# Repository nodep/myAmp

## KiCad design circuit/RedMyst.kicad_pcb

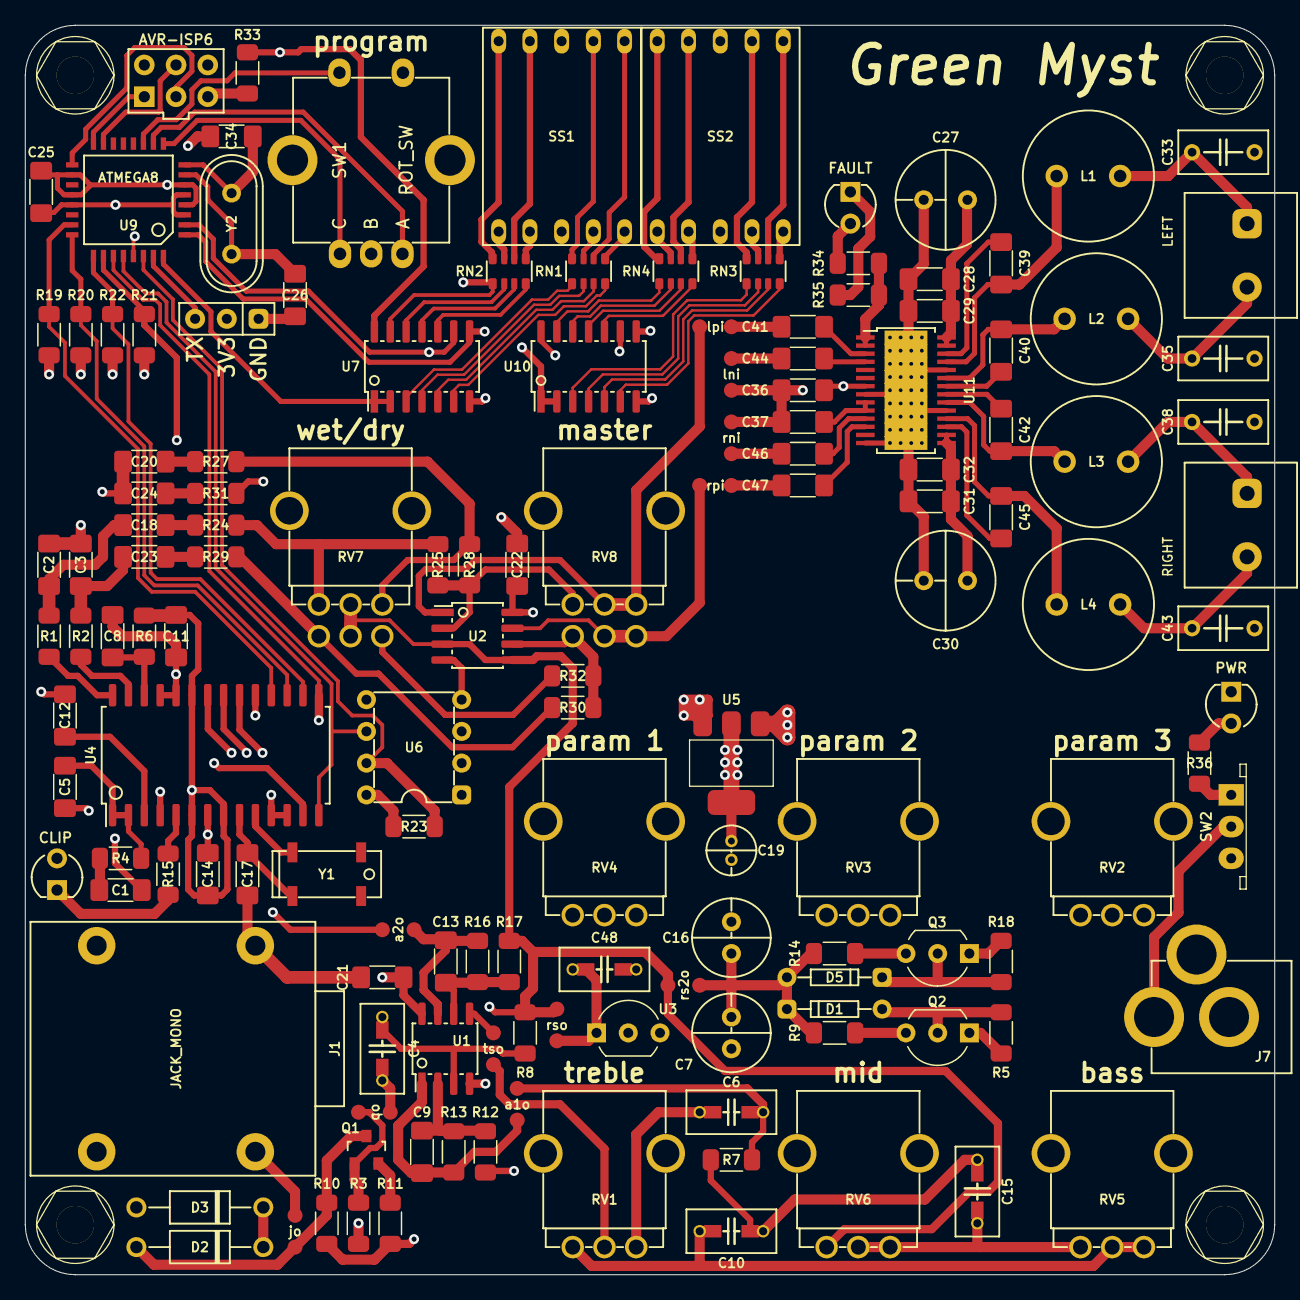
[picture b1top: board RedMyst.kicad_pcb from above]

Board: 4 copper layers, 100.0 x 100.0 mm, 146 parts (0 on the bottom side), 133 nets.

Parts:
C1, C8, C12, C18, C20, C23, C24: 1µF; C_1206
C2, C3: 10nF; C_1206
C4: 1μF; C_5MM_1206
C5, C9, C13, C29, C32: 1nF; C_1206
C6: 250pF; C_5MM_1206
C7, C16: 220μF; CPOL_D6.3_P2.5
C10, C48: 100nF; C_5MM_1206
C11, C14, C21, C22, C25, C28, C31: 100nF; C_1206
C15: 47nF; C_5MM_1206
C17: 15pF; C_1206
C19: 10µf; CPOL_D4_P1.5
C26, C34: 22pF; C_1206
C27, C30: 100μF; CPOL_D8_P3.5
C33, C35, C38, C43: 680nF; C_FILM_5MM
C36, C37, C41, C44, C46, C47: 1μF; C_1206
C39, C40, C42, C45: 220nF; C_1206
D1, D5: 1N4148; DO35
D2, D3: 1N4773a; DO41
D4: CLIP; LED_D3.0mm
D7: FAULT; LED_D3.0mm
D8: PWR; LED_D3.0mm
J1: JACK_MONO; JACK_CL13106
J2: CONN_01X03; PIN_1x03
J3, J4, J5, J6: HOLE; MountingHole
J7: Barrel_Jack_Switch; POWER_JACK_2.1mm
L1, L2, L3, L4: 10μH; COILCRAFT_DR0810
NB1: qo; NET_BRK
NB2: a1o; NET_BRK
NB3: jo; NET_BRK
NB4: tso; NET_BRK
NB5: a2o; NET_BRK
NB6: rso; NET_BRK
NB10: rs2o; NET_BRK
NB16: lpi; NET_BRK
NB17: lni; NET_BRK
NB18: rni; NET_BRK
NB19: rpi; NET_BRK
Q1: MMBFJ201; SOT-23
Q2: BC547; TO-92_Inline_Wide
Q3: BC557; TO-92_Inline_Wide
R1, R2, R4, R12, R17: 1K; R_1206
R3, R11: 1; R_1206
R5, R18: 4K7; R_1206
R6, R15: 100; R_1206
R7: 100K; R_1206
R8, R10: 1M; R_1206
R9, R14: 10; R_1206
R13, R16, R19, R20, R21, R22, R23, R24, R25, R27, R28, R29, R30, R31, R32, R33, R34: 10K; R_1206
R35, R36: 2K2; R_1206
RN1, RN2, RN3, RN4: 100; R_Array_x4_1206
RV1, RV5: 250K; ALPS_RK09L
RV2, RV3, RV4: 50K; ALPS_RK09L
RV6: 10K; ALPS_RK09L
RV7, RV8: 10K; ALPS_RK09L_DBL
S1: LEFT; SPKR_5MM
S2: RIGHT; SPKR_5MM
SS1, SS2: SEVSEG; 7seg_14.2mm
SW1: ROT_SW; ROT_ENC
SW2: ON/OFF; ESP2010_switch
U1, U2: NE5532; SOIC-8_3.9x4.9mm_P1.27mm
U3: TLE2426; TO-92_Inline_Wide
U4: FV-1; SOIC-28_7.5x17.9mm_Pitch1.27mm
U5: LM1117; SOT-223
U6: 24LC32A; DIP-8
U7, U10: 74164; SOIC-14_3.9x8.7mm_P1.27mm
U8: AVR-ISP6; AVR_ISP6
U9: ATMEGA8; TQFP-32_7x7mm_Pitch0.8mm
U11: TPA3136D2; HTSSOP-28_4.4x9.7mm_Pitch0.65mm_ThermalPad
Y1: 32768Hz; QUARTZ_85SMX
Y2: 8MHz; Crystal_HC49-U_Vertical

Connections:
+3V3: C11.1, C14.2, C19.1, C25.2, D4.2, J2.2, R6.1, R21.2, R23.2, R33.2, RV2.1, RV3.1, RV4.1, U4.6, U4.8, U4.23, U5.2, U6.8, U7.14, U8.2, U9.4, U9.6, U9.18, U9.20, U10.14
/AVR_RST: R33.1, U8.5, U9.29
/DBG_TX: J2.3, U9.31
/FV_LOUT: C2.1, C18.1, R1.1
/FV_ROUT: C3.1, C23.1, R2.1
/GVDD: C37.1, U11.9, U11.10
/LED_CK: U7.8, U9.1, U10.8
/LED_DT: U7.1, U7.2, U9.32
/LED_RST: U7.9, U9.2, U10.9
/MID: C12.2, U4.3
/MISO: U8.1, U9.16
/MOSI: U8.4, U9.15
/ROT_SW: SW1.4, U9.11
/S0: R22.1, U4.16, U9.25
/S1: R20.2, U4.17, U9.24
/S2: R19.1, U4.18, U9.23
/SCK: U8.3, U9.17
/SCL: U4.14, U6.6, U9.28
/SDA: U4.15, U6.5, U9.27
/SD_FAULT: R34.2, R35.1, U11.1, U11.2
/T0: R21.1, U4.13, U9.26
/TONE_OUT: C1.2, C20.1, C24.1, NB5.1
/WP: R23.1, U6.7, U9.30
GND: C2.2, C3.2, C5.1, C8.2, C11.2, C12.1, C14.1, C16.2, C17.2, C19.2, C21.1, C22.1, C25.1, C26.2, C27.2, C28.2, C29.2, C30.2, C31.2, C32.2, C33.1, C34.2, C35.2, C36.2, C37.2, C38.1, C43.2, C48.1, D3.2, D8.1, J1.1, J1.3, J1.4, J2.1, J7.2, J7.3, NB17.2, NB18.2, Q3.1, R10.2, R11.2, R18.1, R19.2, R20.1, R22.2, RV2.3, RV3.3, RV4.3, SS1.3, SS1.8, SS2.3, SS2.8, SW1.2, SW1.5, U1.4, U2.4, U3.2, U4.4, U4.7, U4.11, U4.12, U4.19, U4.24, U4.25, U5.1, U6.1, U6.2, U6.3, U6.4, U7.7, U8.6, U9.3, U9.5, U9.21, U10.7, U11.8, U11.14, U11.19, U11.24, U11.29
LOUT: NB16.2, RV8.2, RV8.3, U2.1
unnamed: C1.1, R4.1
unnamed: C4.1, R8.1, U1.3
unnamed: C4.2, NB1.1
unnamed: C5.2, R4.2, U4.1, U4.2
unnamed: C6.1, RV1.3
unnamed: C6.2, NB2.1, R7.2
unnamed: C8.1, R6.2, U4.26
unnamed: C9.1, NB2.2, R13.2, U1.1
unnamed: C9.2, R12.2, R13.1, U1.2
unnamed: C10.1, RV1.1, RV5.2, RV5.3
unnamed: C10.2, C15.1, R7.1
unnamed: C13.1, NB5.2, R16.2, U1.7
unnamed: C13.2, R16.1, R17.1, U1.6
unnamed: C15.2, RV5.1, RV6.2, RV6.3
unnamed: C7.2, C16.1, D1.1, D5.2, NB10.2, R9.1, R14.2
unnamed: C17.1, U4.9, Y1.1
unnamed: C18.2, R24.1
unnamed: C20.2, R27.1
unnamed: C23.2, R29.1
unnamed: C24.2, R31.1
unnamed: C26.1, U9.7, Y2.1
unnamed: C33.2, L1.2, S1.1
unnamed: C34.1, U9.8, Y2.2
unnamed: C35.1, L2.2, S1.2
unnamed: C38.2, L3.2, S2.1
unnamed: C39.1, L1.1, U11.25
unnamed: C39.2, U11.26
unnamed: C40.1, L2.1, U11.23
unnamed: C40.2, U11.22
unnamed: C41.1, U11.3
unnamed: C41.2, NB16.1
unnamed: C42.1, L3.1, U11.20
unnamed: C42.2, U11.21
unnamed: C43.1, L4.2, S2.2
unnamed: C44.1, U11.4
unnamed: C44.2, NB17.1
unnamed: C45.1, L4.1, U11.18
unnamed: C45.2, U11.17
unnamed: C46.1, U11.11
unnamed: C46.2, NB18.1
unnamed: C47.1, U11.12
unnamed: C47.2, NB19.1
unnamed: C48.2, NB6.2, U3.1
unnamed: D1.2, Q2.2, R5.1
unnamed: D2.1, D3.1
unnamed: D2.2, NB3.1, Q1.3, R10.1
unnamed: D4.1, R15.1
unnamed: D5.1, Q3.2, R18.2
unnamed: D7.1, R35.2
unnamed: D8.2, R36.2
unnamed: J1.6, NB3.2
unnamed: J7.1, SW2.2
unnamed: NB1.2, Q1.1, R3.1
unnamed: NB4.1, U1.5
unnamed: NB4.2, RV1.2
unnamed: Q1.2, R11.1
unnamed: Q2.3, R9.2
unnamed: Q3.3, R14.1
unnamed: R1.2, U4.28
unnamed: R2.2, U4.27
unnamed: R15.2, U4.5
unnamed: R24.2, R25.1, RV7.1
unnamed: R25.2, R28.2, RV8.1, U2.2
unnamed: R27.2, R28.1, RV7.3
unnamed: R29.2, R30.1, RV7.4
unnamed: R30.2, R32.2, RV8.4, U2.6
unnamed: R31.2, R32.1, RV7.6
unnamed: RN1.1, U7.3
unnamed: RN1.2, U7.4
unnamed: RN1.3, U7.5
unnamed: RN1.4, U7.6
unnamed: RN1.5, SS1.5
unnamed: RN1.6, SS1.6
unnamed: RN1.7, SS1.4
unnamed: RN1.8, SS1.7
unnamed: RN2.1, U7.13, U10.1, U10.2
unnamed: RN2.2, U7.12
unnamed: RN2.3, U7.11
unnamed: RN2.4, U7.10
unnamed: RN2.5, SS1.2
unnamed: RN2.6, SS1.9
unnamed: RN2.7, SS1.1
unnamed: RN2.8, SS1.10
unnamed: RN3.1, U10.3
unnamed: RN3.2, U10.4
unnamed: RN3.3, U10.5
unnamed: RN3.4, U10.6
unnamed: RN3.5, SS2.5
unnamed: RN3.6, SS2.6
unnamed: RN3.7, SS2.4
unnamed: RN3.8, SS2.7
unnamed: RN4.1, U10.13
unnamed: RN4.2, U10.12
unnamed: RN4.3, U10.11
unnamed: RN4.4, U10.10
unnamed: RN4.5, SS2.2
unnamed: RN4.6, SS2.9
unnamed: RN4.7, SS2.1
unnamed: RN4.8, SS2.10
unnamed: RV2.2, U4.22
unnamed: RV3.2, U4.21
unnamed: RV4.2, U4.20
unnamed: SW1.1, U9.10
unnamed: SW1.3, U9.9
unnamed: U4.10, Y1.2
ROUT: NB19.2, RV8.5, RV8.6, U2.7
VDD: C7.1, C21.2, C22.2, C27.1, C28.1, C29.1, C30.1, C31.1, C32.1, C36.1, D7.2, Q2.1, R3.2, R5.2, R34.1, R36.1, SW2.1, U1.8, U2.8, U3.3, U5.3, U11.7, U11.15, U11.16, U11.27, U11.28
VGND: NB6.1, NB10.1, R8.2, R12.1, R17.2, RV6.1, RV7.2, RV7.5, U2.3, U2.5

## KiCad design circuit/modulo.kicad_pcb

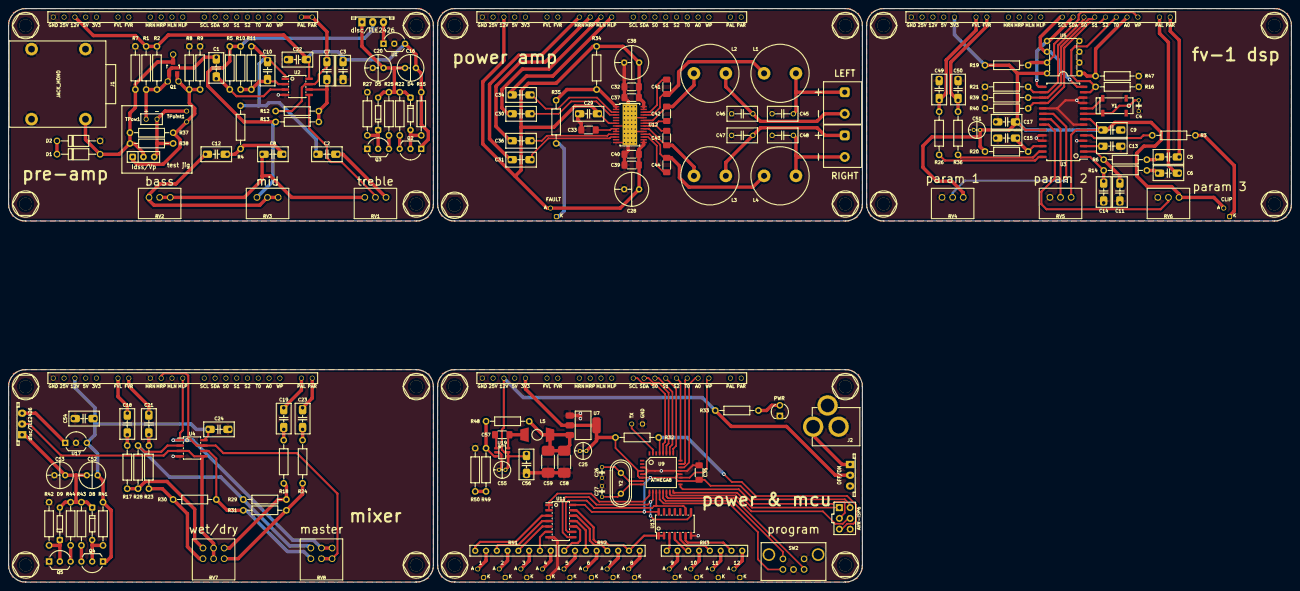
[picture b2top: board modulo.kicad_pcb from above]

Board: 2 copper layers, 302.0 x 135.0 mm, 201 parts (0 on the bottom side), 150 nets.

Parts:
C1, C29, C30, C31, C34, C36: 1μF; C_5MM_1206
C2: 680pF; C_5MM_1206
C3, C9, C17, C22, C24, C54, C56: 100nF; C_5MM_1206
C4: 15pF; C_2.5MM
C5, C6, C13, C15, C18, C19, C21, C23: 1µF; C_5MM_1206
C7, C10, C11, C14: 1nF; C_5MM_1206
C8: 250nF; C_5MM_1206
C12: 47nF; C_5MM_1206
C16, C20, C52, C53: 220μF; CPOL_D6.3_P2.5
C25: 10µf; CPOL_D4_P1.5
C26, C27: 22pF; C_2.5MM
C28, C38: 100μF; CPOL_D8_P3.5
C32, C35, C39, C57: 100nF; C_1206
C33: 1μF; C_1206
C37, C40: 1nF; C_1206
C41, C42, C43, C44: 220nF; C_1206
C45, C46, C47, C48: 680nF; C_FILM_5MM
C49, C50: 10nF; C_5MM_1206
C51: 10µF; CPOL_D4_P1.5
C55: 4.7µf; CPOL_D4_P1.5
C58, C59: 15µf; C_1812
D1, D2: 1N4773a; DO41
D3: CLIP; LED_D3.0mm_PCBedge
D4, D5, D8, D9: 1N4148; DO35
D6: FAULT; LED_D3.0mm_PCBedge
D7: PWR; LED_D3.0mm
D10: 1; LED_D3.0mm_PCBedge
D11: 2; LED_D3.0mm_PCBedge
D12: 3; LED_D3.0mm_PCBedge
D13: 4; LED_D3.0mm_PCBedge
D14: 5; LED_D3.0mm_PCBedge
D15: 6; LED_D3.0mm_PCBedge
D16: 7; LED_D3.0mm_PCBedge
D17: 8; LED_D3.0mm_PCBedge
D18: 9; LED_D3.0mm_PCBedge
D19: 10; LED_D3.0mm_PCBedge
D20: 11; LED_D3.0mm_PCBedge
D21: 12; LED_D3.0mm_PCBedge
J1: JACK_MONO; JACK_CL13106
J2: Barrel_Jack_Switch; POWER_JACK_2.1mm
J3, J4, J5, J6, J7, J8, J9, J10, J11, J12, J13, J14, J15, J17, J18, J19, J24, J25, J26, J27: HOLE; MountingHole
L1, L2, L3, L4: 10μH; COILCRAFT_RFS1412
L5: 33µH; COIL_SRR6603
Q1: MMBFJ201; SOT-23_with_jig
Q2, Q4: BC547; TO-92_Inline_Wide
Q3, Q5: BC557; TO-92_Inline_Wide
R1: 15K; R_10MM
R2, R5, R7, R9, R37: 1M; R_10MM
R3, R20, R38: 100; R_10MM
R4: 100K; R_10MM
R6, R10, R13, R14, R26, R36: 1K; R_10MM
R8: 1K5; R_10MM
R11, R12, R16, R17, R18, R19, R21, R23, R24, R28, R29, R30, R31, R32, R34, R39, R40, R47, R49, R50: 10K; R_10MM
R15, R27, R41, R42: 4K7; R_10MM
R22, R25, R43, R44: 10; R_10MM
R33, R35: 2K2; R_10MM
R48: 75K; R_10MM
RN1, RN2, RN3: 100; R_Array_x4_P2.54
RV1, RV2: A100K; BOURNS_PTD901_xx15K
RV3: 10K; BOURNS_PTD901_xx15K
RV4, RV5, RV6: 50K; BOURNS_PTD901_xx15K
RV7, RV8: 10K; BOURNS_PTD902_xx15K
S1: LEFT; SPKR_5MM
S2: RIGHT; SPKR_5MM
SW1: OFF/ON; ESP2010_switch
SW2: ROT_SW; BOURNS_PEC12R_2x17F
SW3: Idss/Vp; PIN_1x03
SW4, SW5: disc/TLE2426; ESP2010_switch
TPoint1: CONN_01X02; TestPoints
TPow1: TestDC; TestPower
U1, U17: TLE2426; TO-92_Inline_Wide
U2, U4: NE5532; SOIC-8_3.9x4.9mm_P1.27mm
U3: FV-1; SOIC-28_7.5x17.9mm_Pitch1.27mm
U5: 24LC32A; DIP-8
U6, U8, U14, U15, U16: modulo-bus
U7: LM1117; SOT-223
U9: ATMEGA8; TQFP-32_7x7mm_Pitch0.8mm
U10: AVR-ISP6; AVR_ISP6_horizontal
U11, U13: 74164; SOIC-14_3.9x8.7mm_P1.27mm
U12: TPA3136D2; HTSSOP-28_4.4x9.7mm_Pitch0.65mm_ThermalPad
U18: DBG_UART
U19: TPS560430; SOT-23-6
Y1: 32768Hz; QUARTZ_85SMX
Y2: 8MHz; Crystal_HC49-U_Vertical

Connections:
+3V3: C9.2, C17.1, C25.1, C35.2, C51.1, D3.2, R19.2, R20.1, R32.2, RV4.3, RV5.3, RV6.3, U3.6, U3.8, U3.23, U5.8, U7.2, U8.5, U9.4, U9.6, U9.18, U9.20, U10.2, U11.14, U13.14, U15.5
+12V: C3.2, C16.1, C22.2, C24.2, C28.1, C29.1, C32.1, C37.1, C38.1, C39.1, C40.1, C52.1, C54.2, C55.1, C56.1, D6.2, Q2.1, Q4.1, R1.2, R2.2, R15.2, R33.1, R34.1, R41.2, SW1.2, U1.3, U2.8, U4.8, U6.3, U8.3, U12.7, U12.15, U12.16, U12.27, U12.28, U14.3, U16.3, U17.3, U19.4, U19.5
/Class D audio power amp/GVDD: C33.1, U12.9, U12.10
/Class D audio power amp/SD_FAULT: R34.2, R35.1, U12.1, U12.2
/FV-1/A0: R47.1, U5.1, U15.20
/FV-1/FV_LIN: C6.2, U15.6
/FV-1/FV_LOUT: C49.1, R26.1, U15.8
/FV-1/FV_RIN: C5.2, U15.7
/FV-1/FV_ROUT: C50.1, R36.1, U15.9
/FV-1/MID: C13.2, U3.3
/FV-1/REFP: C15.1, R20.2, U3.26
/FV-1/S0: R21.1, U3.16, U15.12
/FV-1/S1: R39.2, U3.17, U15.13
/FV-1/S2: R40.1, U3.18, U15.14
/FV-1/SCL: U3.14, U5.6, U15.10
/FV-1/SDA: U3.15, U5.5, U15.11
/FV-1/T0: R16.1, U3.13, U15.15
/FV-1/WP: R19.1, U5.7, U15.21
/mixer/FVL: C18.1, U16.8
/mixer/FVR: C21.1, U16.9
/mixer/MIXL: RV8.2, RV8.3, U4.1, U16.16
/mixer/MIXR: RV8.5, RV8.6, U4.7, U16.18
/mixer/MIX_VGND: RV7.2, RV7.5, SW5.2, U4.3, U4.5
/mixer/PAL: C19.1, U16.6
/mixer/PAR: C23.1, U16.7
/mixer/vgnd_disc: C52.2, C53.1, D8.1, D9.2, R43.1, R44.2, SW5.1
/mixer/vgnd_tle: SW5.3, U17.1
/power and MCU/4.75V: C58.1, C59.1, L5.2, R48.2, U7.3
/power and MCU/A0: U8.20, U9.22
/power and MCU/AVR_RST: R32.1, U9.29, U10.5
/power and MCU/CB: C57.1, U19.1
/power and MCU/DBG_TX: U9.31, U18.2
/power and MCU/FB: R48.1, R49.2, U19.3
/power and MCU/LED_CK: U9.10, U11.8, U13.8
/power and MCU/LED_DT: U9.9, U11.1, U11.2
/power and MCU/LED_RST: U9.11, U11.9, U13.9
/power and MCU/MISO: U9.16, U10.1
/power and MCU/MOSI: U9.15, U10.4
/power and MCU/ROT_A: SW2.1, U9.12
/power and MCU/ROT_B: SW2.3, U9.14
/power and MCU/ROT_SW: SW2.4, U9.13
/power and MCU/S0: U8.12, U9.26
/power and MCU/S1: U8.13, U9.25
/power and MCU/S2: U8.14, U9.24
/power and MCU/SCK: U9.17, U10.3
/power and MCU/SCL: U8.10, U9.28
/power and MCU/SDA: U8.11, U9.27
/power and MCU/SW: C57.2, L5.1, U19.6
/power and MCU/T0: U8.15, U9.23
/power and MCU/WP: U8.21, U9.19
/pre amp/PA_OUT: C7.1, R12.2, U2.7, U14.6, U14.7
/pre amp/PA_VGND: R5.2, R10.1, R13.2, RV3.1, SW4.2
/pre amp/jfet_d: C1.2, Q1.1, R1.1, R2.1, TPow1.1
/pre amp/jfet_g: D1.2, J1.6, Q1.3, R7.1, R37.1, R38.2, SW3.2
/pre amp/jfet_s: Q1.2, R8.1, R9.1, R37.2, SW3.1, TPoint1.1
/pre amp/vgnd_disc: C16.2, C20.1, D4.1, D5.2, R22.1, R25.2, SW4.1
/pre amp/vgnd_tle: SW4.3, U1.1
GND: C3.1, C4.2, C9.1, C11.1, C13.1, C14.1, C15.2, C17.2, C20.2, C22.1, C24.1, C25.2, C26.2, C27.2, C28.2, C29.2, C32.2, C33.2, C35.1, C37.2, C38.2, C39.2, C40.2, C45.1, C46.2, C47.1, C48.2, C49.2, C50.2, C51.2, C53.2, C54.1, C55.2, C56.2, C58.2, C59.2, D2.2, D7.1, D10.1, D11.1, D12.1, D13.1, D14.1, D15.1, D16.1, D17.1, D18.1, D19.1, D20.1, D21.1, J1.1, J1.3, J1.4, J2.2, J2.3, Q3.1, Q5.1, R7.2, R8.2, R9.2, R16.2, R21.2, R27.1, R39.1, R40.2, R42.1, R47.2, R50.1, RV4.1, RV5.1, RV6.1, SW2.2, SW2.5, U1.2, U2.4, U3.4, U3.7, U3.11, U3.12, U3.19, U3.24, U3.25, U4.4, U5.2, U5.3, U5.4, U6.1, U7.1, U8.1, U9.3, U9.5, U9.21, U10.6, U11.7, U12.8, U12.14, U12.19, U12.24, U12.29, U13.7, U14.1, U15.1, U16.1, U16.17, U16.19, U17.2, U18.1, U19.2
unnamed: C1.1, R5.1, U2.3
unnamed: C2.1, RV1.3
unnamed: C4.1, U3.9, Y1.1
unnamed: C5.1, R6.1
unnamed: C6.1, R14.1
unnamed: C7.2, R12.1, R13.1, U2.6
unnamed: C8.1, RV1.1, RV2.2, RV2.3
unnamed: C2.2, C10.1, R4.2, R11.2, U2.1
unnamed: C10.2, R10.2, R11.1, U2.2
unnamed: C11.2, R6.2, U3.2
unnamed: C8.2, C12.1, R4.1
unnamed: C12.2, RV2.1, RV3.2, RV3.3
unnamed: C14.2, R14.2, U3.1
unnamed: C18.2, R17.1
unnamed: C19.2, R18.1
unnamed: C21.2, R23.1
unnamed: C23.2, R24.1
unnamed: C26.1, U9.7, Y2.1
unnamed: C27.1, U9.8, Y2.2
unnamed: C30.1, U12.4
unnamed: C30.2, U6.17
unnamed: C31.1, U12.12
unnamed: C31.2, U6.19
unnamed: C34.1, U12.3
unnamed: C34.2, U6.16
unnamed: C36.1, U12.11
unnamed: C36.2, U6.18
unnamed: C41.1, L1.1, U12.25
unnamed: C41.2, U12.26
unnamed: C42.1, L2.1, U12.23
unnamed: C42.2, U12.22
unnamed: C43.1, L3.1, U12.20
unnamed: C43.2, U12.21
unnamed: C44.1, L4.1, U12.18
unnamed: C44.2, U12.17
unnamed: C45.2, L1.2, S1.1
unnamed: C46.1, L2.2, S1.2
unnamed: C47.2, L3.2, S2.1
unnamed: C48.1, L4.2, S2.2
unnamed: D1.1, D2.1
unnamed: D3.1, R3.1
unnamed: D4.2, Q2.2, R15.1
unnamed: D5.1, Q3.2, R27.2
unnamed: D6.1, R35.2
unnamed: D7.2, R33.2
unnamed: D8.2, Q4.2, R41.1
unnamed: D9.1, Q5.2, R42.2
unnamed: D10.2, RN1.2
unnamed: D11.2, RN1.4
unnamed: D12.2, RN1.6
unnamed: D13.2, RN1.8
unnamed: D14.2, RN2.2
unnamed: D15.2, RN2.4
unnamed: D16.2, RN2.6
unnamed: D17.2, RN2.8
unnamed: D18.2, RN3.2
unnamed: D19.2, RN3.4
unnamed: D20.2, RN3.6
unnamed: D21.2, RN3.8
unnamed: J2.1, SW1.1
unnamed: Q2.3, R22.2
unnamed: Q3.3, R25.1
unnamed: Q4.3, R43.2
unnamed: Q5.3, R44.1
unnamed: R3.2, U3.5
unnamed: R17.2, R28.1, RV7.1
unnamed: R18.2, R29.1, RV7.3
unnamed: R23.2, R30.1, RV7.4
unnamed: R24.2, R31.1, RV7.6
unnamed: R26.2, U3.28
unnamed: R28.2, R29.2, RV8.1, U4.2
unnamed: R30.2, R31.2, RV8.4, U4.6
unnamed: R36.2, U3.27
unnamed: R38.1, SW3.3, TPoint1.2, TPow1.2
unnamed: R49.1, R50.2
unnamed: RN1.1, U11.3
unnamed: RN1.3, U11.4
unnamed: RN1.5, U11.5
unnamed: RN1.7, U11.6
unnamed: RN2.1, U11.10
unnamed: RN2.3, U11.11
unnamed: RN2.5, U11.12
unnamed: RN2.7, U11.13, U13.1, U13.2
unnamed: RN3.1, U13.3
unnamed: RN3.3, U13.4
unnamed: RN3.5, U13.5
unnamed: RN3.7, U13.6
unnamed: RV1.2, U2.5
unnamed: RV4.2, U3.20
unnamed: RV5.2, U3.21
unnamed: RV6.2, U3.22
unnamed: U3.10, Y1.2

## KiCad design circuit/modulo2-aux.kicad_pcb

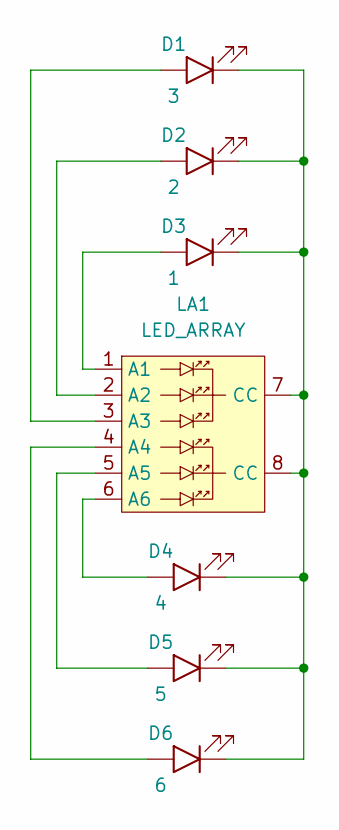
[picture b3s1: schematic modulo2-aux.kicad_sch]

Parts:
D1: 3; LED_D3.0mm
D2: 2; LED_D3.0mm
D3: 1; LED_D3.0mm
D4: 4; LED_D3.0mm
D5: 5; LED_D3.0mm
D6: 6; LED_D3.0mm
LA1: LED_ARRAY

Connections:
unnamed: D1.1 (K), D2.1 (K), D3.1 (K), D4.1 (K), D5.1 (K), D6.1 (K), LA1.7 (CC), LA1.8 (CC)
unnamed: D1.2 (A), LA1.3 (A3)
unnamed: D2.2 (A), LA1.2 (A2)
unnamed: D3.2 (A), LA1.1 (A1)
unnamed: D4.2 (A), LA1.6 (A6)
unnamed: D5.2 (A), LA1.5 (A5)
unnamed: D6.2 (A), LA1.4 (A4)

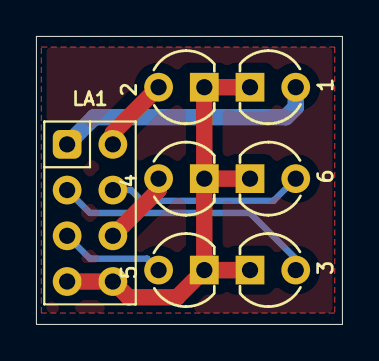
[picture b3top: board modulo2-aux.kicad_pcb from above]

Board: 2 copper layers, 17.0 x 16.0 mm, 7 parts (0 on the bottom side), 7 nets.

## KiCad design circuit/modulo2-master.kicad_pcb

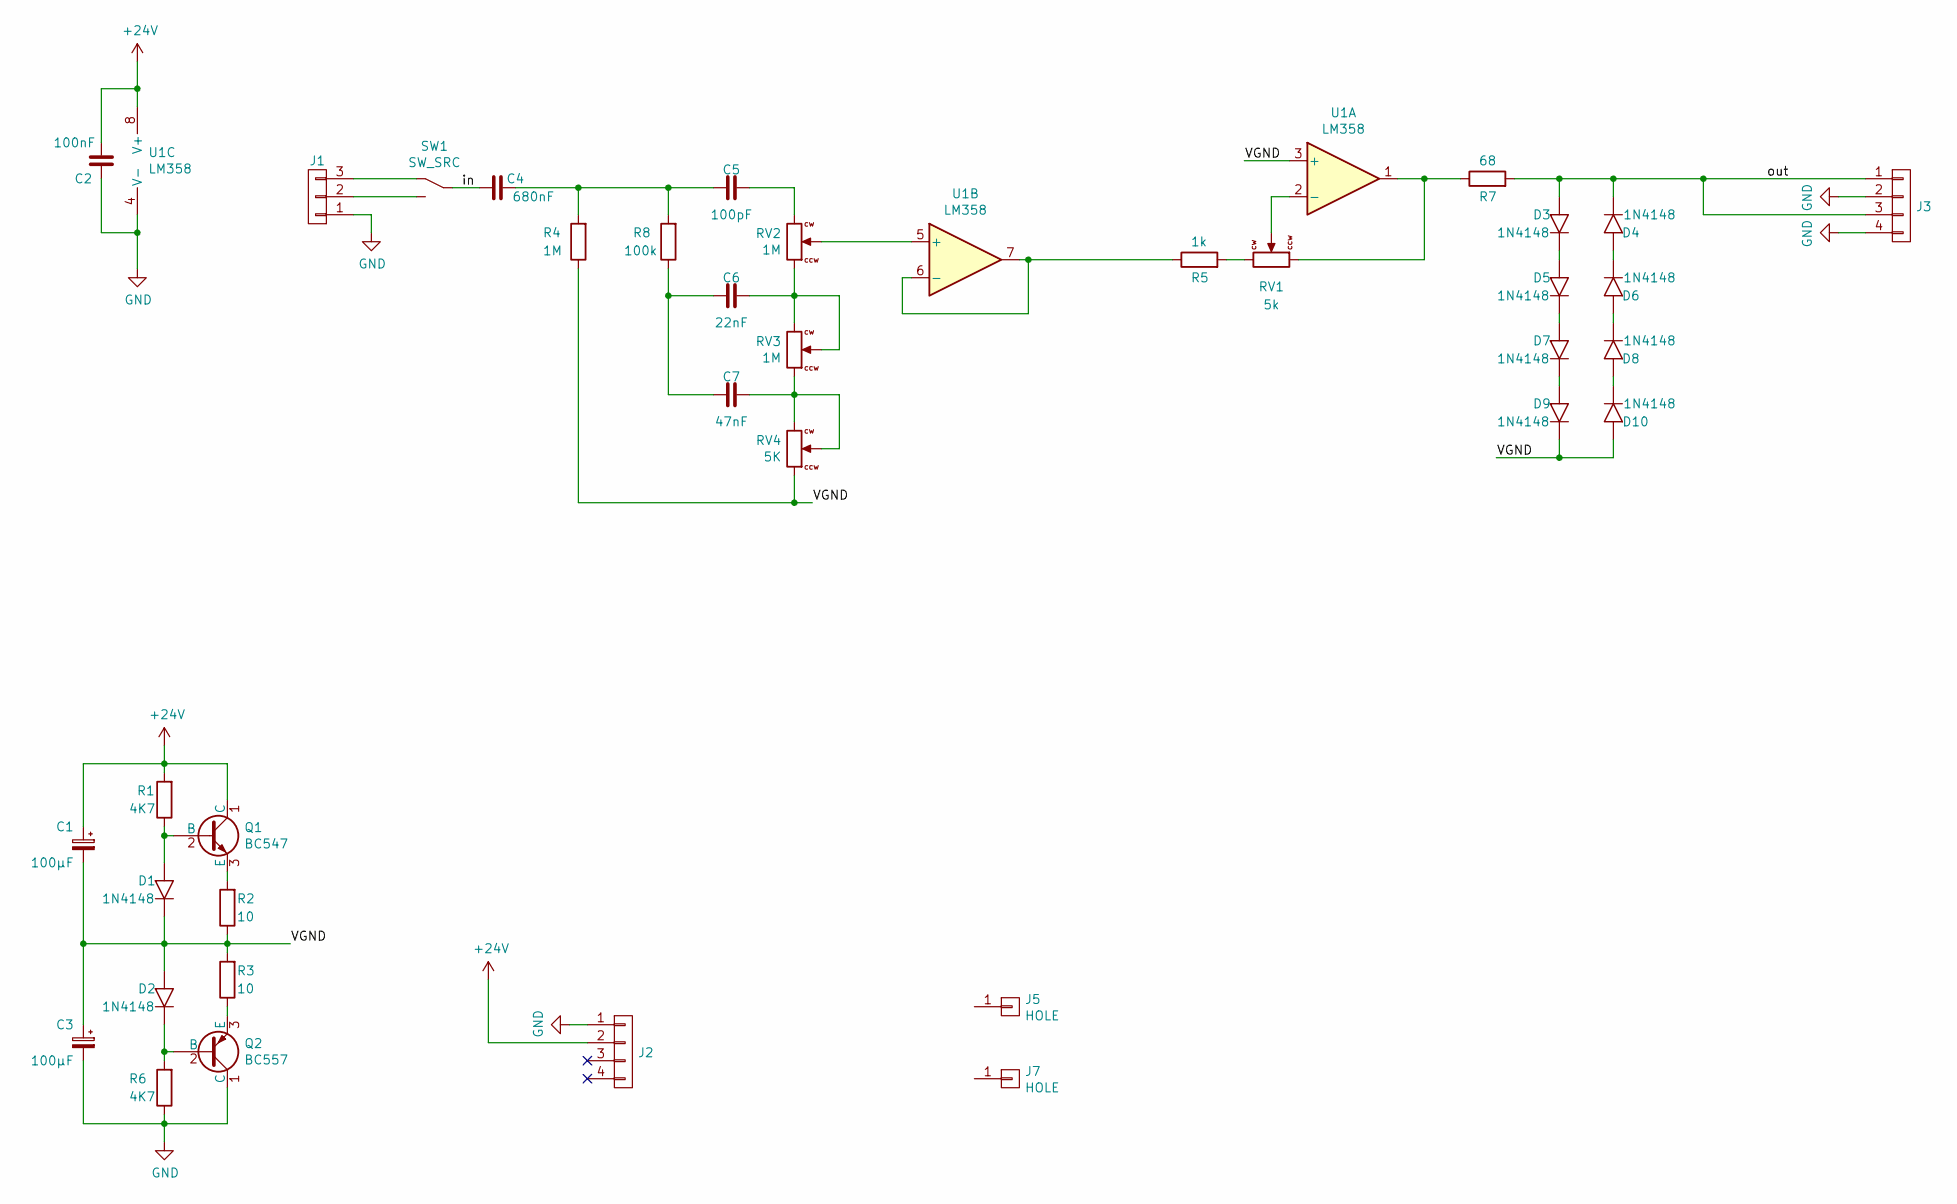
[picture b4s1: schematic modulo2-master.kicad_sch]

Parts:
C1, C3: 100μF; CPOL_D6.3_P2.5
C2: 100nF; C_FILM_L7.2mm_W3.5mm_P5.00mm
C4: 680nF; C_FILM_L7.2mm_W5.5mm_P5.00mm
C5: 100pF; C_5MM_1206
C6: 22nF; C_5MM_1206
C7: 47nF; C_5MM_1206
D1, D2, D3, D4, D5, D6, D7, D8, D9, D10: 1N4148; DO35
J1: CONN_01X03; PIN_1x03
J2, J3: CONN_01X04; PIN_1x04
J5, J7: HOLE; MountingHole
Q1: BC547; TO-92_Inline_Wide
Q2: BC557; TO-92_Inline_Wide
R1, R6: 4K7; R_10MM
R2, R3: 10; R_10MM
R4: 1M; R_10MM
R5: 1k; R_10MM
R7: 68; R_10MM
R8: 100k; R_10MM
RV1: 5k; POT_VULGARIS
RV2, RV3: 1M; POT_VULGARIS
RV4: 5K; POT_VULGARIS
SW1: SW_SRC; ESP2010_switch
U1: LM358; SOIC-8_3.9x4.9mm_P1.27mm

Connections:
+24V: C1.1, C2.2, J2.2, Q1.1 (C), R1.2, U1.8 (V+)
/VGND: C1.2, C3.1, D1.1 (K), D2.2 (A), D9.1 (K), D10.2 (A), R2.1, R3.2, R4.1, RV4.1, U1.3 (+)
/in: C4.1, SW1.2
/out: D3.2 (A), D4.1 (K), J3.1, J3.3, R7.2
GND: C2.1, C3.2, J1.1, J2.1, J3.2, J3.4, Q2.1 (C), R6.1, U1.4 (V-)
unnamed: C4.2, C5.1, R4.2, R8.2
unnamed: C5.2, RV2.3
unnamed: C6.1, C7.1, R8.1
unnamed: C6.2, RV2.1, RV3.2, RV3.3
unnamed: C7.2, RV3.1, RV4.2, RV4.3
unnamed: D1.2 (A), Q1.2 (B), R1.1
unnamed: D2.1 (K), Q2.2 (B), R6.2
unnamed: D3.1 (K), D5.2 (A)
unnamed: D4.2 (A), D6.1 (K)
unnamed: D5.1 (K), D7.2 (A)
unnamed: D6.2 (A), D8.1 (K)
unnamed: D7.1 (K), D9.2 (A)
unnamed: D8.2 (A), D10.1 (K)
unnamed: J1.2, SW1.3
unnamed: J1.3, SW1.1
unnamed: Q1.3 (E), R2.2
unnamed: Q2.3 (E), R3.1
unnamed: R5.1, U1.6 (-), U1.7
unnamed: R5.2, RV1.3
unnamed: R7.1, RV1.1, U1.1
unnamed: RV1.2, U1.2 (-)
unnamed: RV2.2, U1.5 (+)

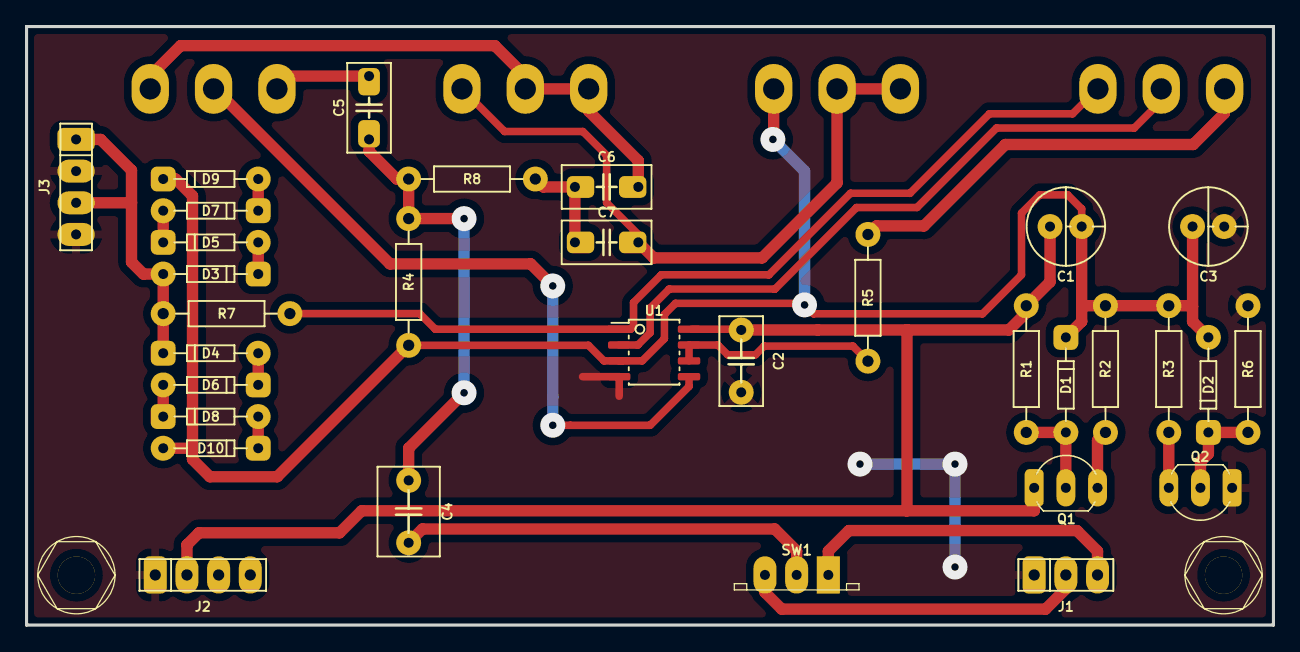
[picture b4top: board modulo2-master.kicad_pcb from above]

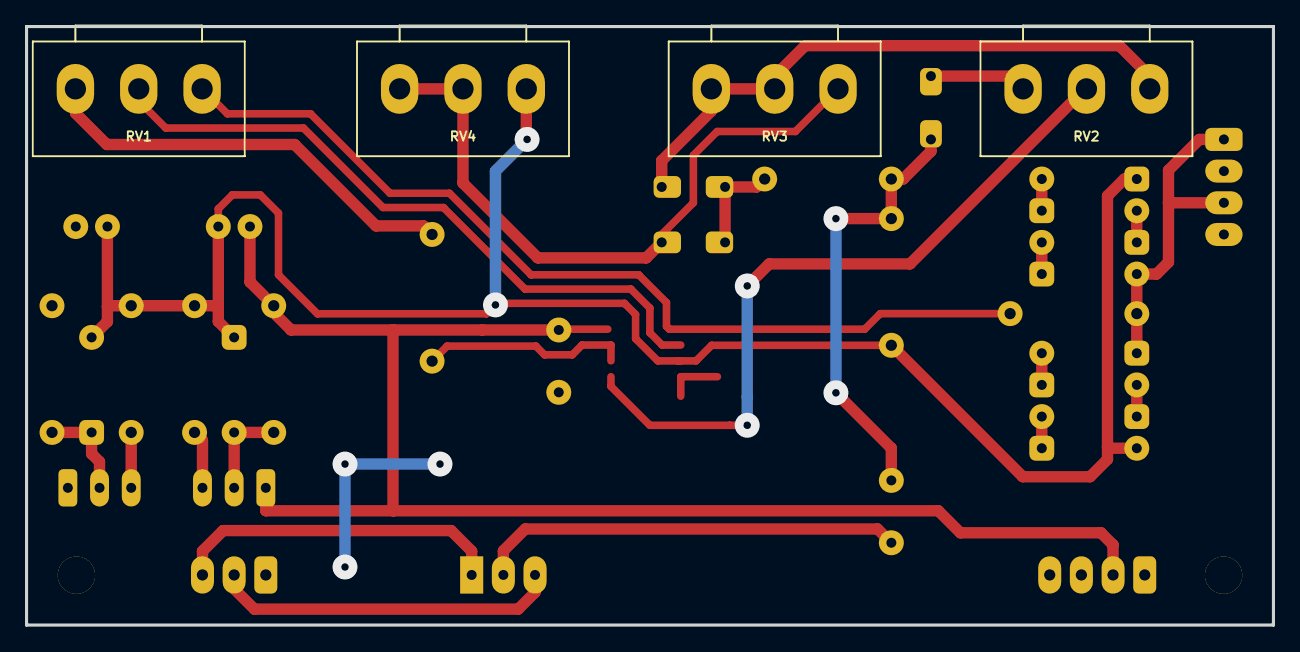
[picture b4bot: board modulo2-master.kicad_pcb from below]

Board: 2 copper layers, 100.0 x 48.0 mm, 38 parts (4 on the bottom side), 27 nets.

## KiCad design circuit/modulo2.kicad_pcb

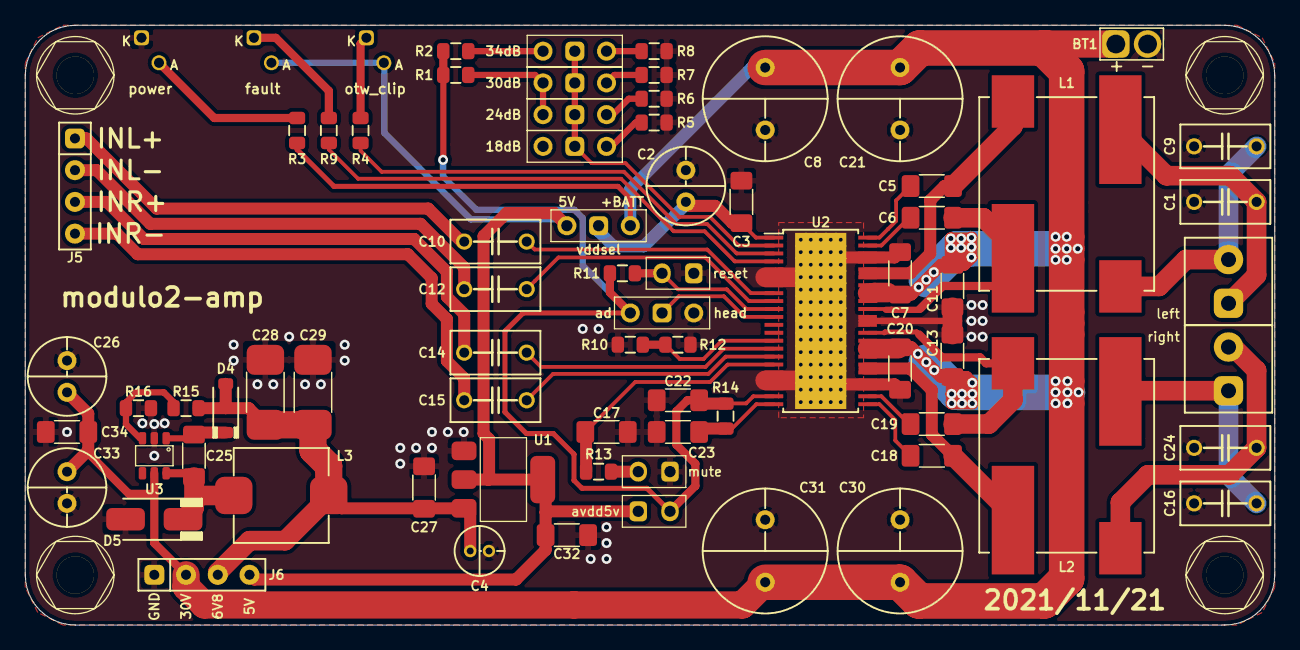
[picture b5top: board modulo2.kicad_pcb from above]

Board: 2 copper layers, 100.0 x 48.0 mm, 79 parts (0 on the bottom side), 47 nets.

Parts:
BT1: BATT; BATTERY
C1, C9, C10, C12, C14, C15, C16, C24: 1μF; C_FILM_5MM
C2: 470μF; CPOL_D6.3_P2.5
C3, C25, C27, C32, C34: 100nF; C_1206
C4: 10μF; CPOL_D4_P1.5
C5, C6, C17, C18, C19: 33nF; C_1206
C7, C11, C13, C20, C22, C23: 1μF; C_1206
C8, C21, C30, C31: 220μF; CPOL_D10_P5
C26, C33: 20μF; CPOL_D6.3_P2.5
C28, C29: 10μF; C_1812
D1: power; LED_D3.0mm_PCBedge
D2: otw_clip; LED_D3.0mm_PCBedge
D3: fault; LED_D3.0mm_PCBedge
D4: 1N4148; D_SOD-123
D5: SS18A; D_SMA
J1, J2, J3, J4: HOLE; MountingHole
J5, J6: CONN_01X04; PIN_1x04
L1, L2: 10μH; COILCRAFT-UA801x-AL
L3: 27μH; COIL_DER0705
R1, R10, R12: 100K; R_0805
R2, R15: 75K; R_0805
R3, R16: 10K; R_0805
R4, R9, R13: 1K; R_0805
R5: 5K6; R_0805
R6: 20K; R_0805
R7: 39K; R_0805
R8, R11: 47K; R_0805
R14: 3R3; R_0805
S1: 18dB; JUMPER_3WAY
S2: 24dB; JUMPER_3WAY
S3: 30dB; JUMPER_3WAY
S4: 34dB; JUMPER_3WAY
SPK1: left; SPKR_3.5MM
SPK2: right; SPKR_3.5MM
SW1: reset; Switch_2.5mm
SW2: mute; Switch_2.5mm
SW3: HEAD/AD; SW_SPDT_JUMPER
SW4: vddsel; SW_SPDT_JUMPER
SW5: avdd5v; Switch_2.5mm
U1: LM1117-5.0; SOT-223
U2: TPA3220; TSSOP-44_4.4x9.7mm_Pitch0.635mm_ThermalPad
U3: MCP16331; SOT-23-6

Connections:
6V8: C4.1, C27.2, C28.2, C29.2, D4.2, J6.3, L3.2, R15.1, U1.3
+5V: C32.2, D2.2, D3.2, J6.4, SW4.3, SW5.1, U1.2
+BATT: BT1.1, C7.2, C8.1, C11.1, C13.1, C20.1, C21.1, C26.1, C30.1, C31.1, C33.1, C34.2, J6.2, R3.1, SW4.1, U2.29, U2.30, U2.31, U2.36, U2.37, U2.38, U3.5
/power amp/AVDD: C22.1, R1.1, R2.1, R11.2, R14.2, SW3.1, SW5.2, U2.21
/power amp/CMUTE: C17.1, R13.1, U2.17
/power amp/FREQ_ADJ: R10.2, R12.2, U2.14
/power amp/GVDD: C23.1, R14.1, U2.22
/power amp/OUT1_M: C6.2, L1.3, U2.35
/power amp/OUT1_P: C5.2, L1.2, U2.39, U2.40
/power amp/OUT2_M: C18.1, L2.3, U2.27, U2.28
/power amp/OUT2_P: C19.1, L2.2, U2.32
/power amp/RESET: R11.1, SW1.2, U2.10
/power amp/VDD: C2.1, C3.2, SW4.2, U2.1
FAULT: R9.1, U2.4
GND: BT1.2, C1.2, C2.2, C3.1, C4.2, C7.1, C8.2, C9.1, C11.2, C13.2, C16.2, C17.2, C20.2, C21.2, C22.2, C23.2, C24.1, C26.2, C27.1, C28.1, C29.1, C30.2, C31.2, C32.1, C33.2, C34.1, D1.1, D5.2, J6.1, R5.2, R6.2, R7.2, R8.2, R10.1, R12.1, R16.2, SW1.1, SW2.1, SW3.3, U1.1, U2.5, U2.6, U2.7, U2.18, U2.19, U2.20, U2.25, U2.26, U2.33, U2.34, U2.41, U2.42, U2.45, U3.2
HEAD: SW3.2, U2.11
unnamed: C1.1, L1.1, SPK1.1
unnamed: C5.1, U2.44
unnamed: C6.1, U2.43
unnamed: C9.2, L1.4, SPK1.2
unnamed: C10.1, J5.1
unnamed: C10.2, U2.8
unnamed: C12.1, J5.2
unnamed: C12.2, U2.9
unnamed: C14.1, J5.3
unnamed: C14.2, U2.15
unnamed: C15.1, J5.4
unnamed: C15.2, U2.16
unnamed: C16.1, L2.1, SPK2.1
unnamed: C18.2, U2.23
unnamed: C19.2, U2.24
unnamed: C24.2, L2.4, SPK2.2
unnamed: C25.1, D5.1, L3.1, U3.6
unnamed: C25.2, D4.1, U3.1
unnamed: D1.2, R3.2
unnamed: D2.1, R4.2
unnamed: D3.1, R9.2
unnamed: R1.2, S2.1, S3.1
unnamed: R2.2, S4.1
unnamed: R5.1, S1.3
unnamed: R6.1, S2.3
unnamed: R7.1, S3.3
unnamed: R8.1, S4.3
unnamed: R13.2, SW2.2
unnamed: R15.2, R16.1, U3.3
unnamed: S1.2, S2.2, S3.2, S4.2, U2.2
OTW_CLIP: R4.1, U2.3
